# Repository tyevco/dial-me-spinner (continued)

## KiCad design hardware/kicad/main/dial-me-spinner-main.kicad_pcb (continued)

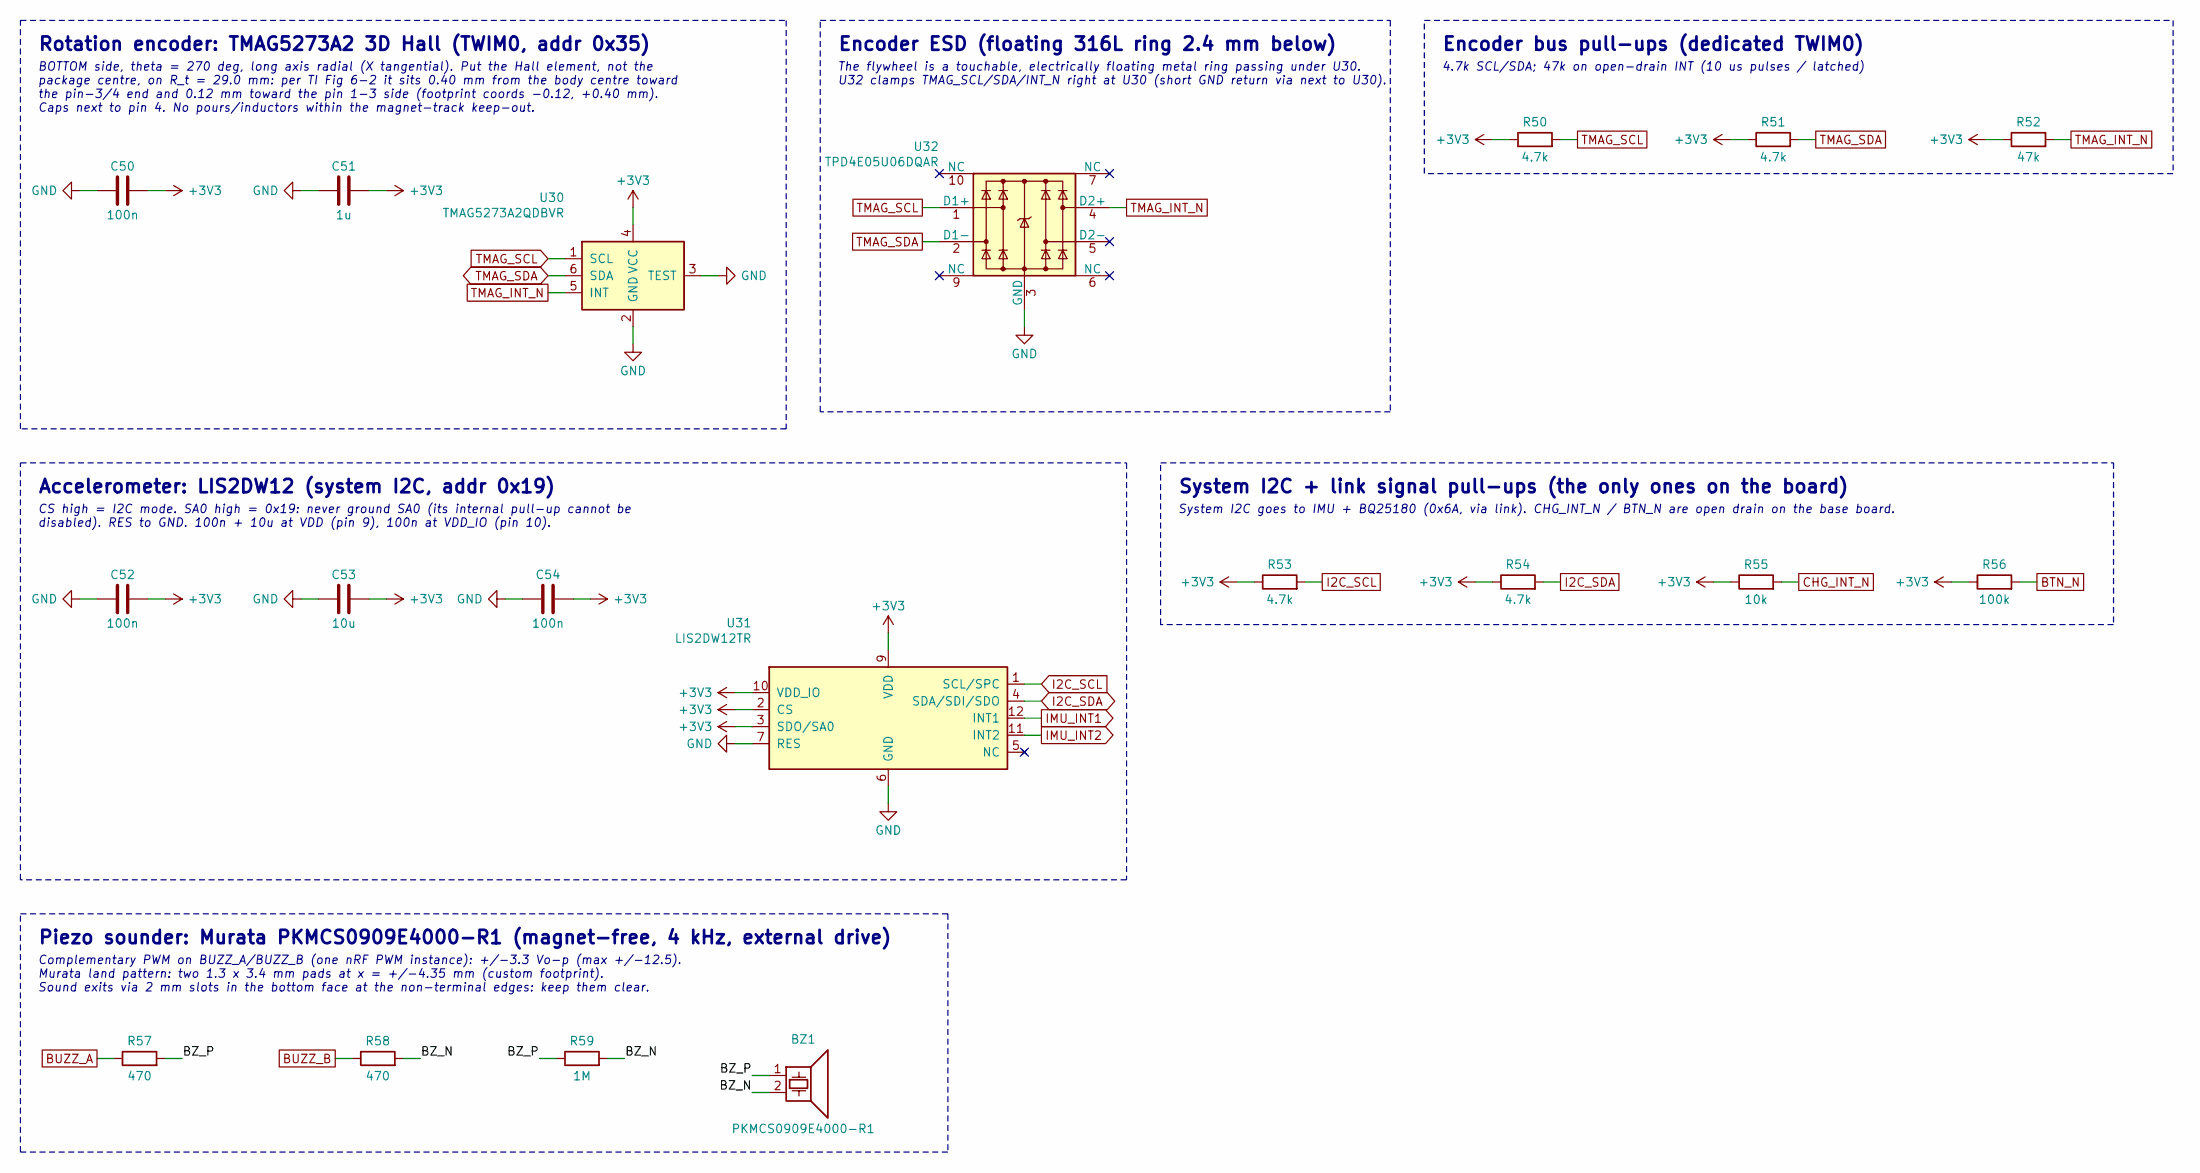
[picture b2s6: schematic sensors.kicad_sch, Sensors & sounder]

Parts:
BZ1: PKMCS0909E4000-R1; Buzzer_Murata_PKMCS0909E4000-R1; MPN PKMCS0909E4000-R1; LCSC C910763
C50, C52, C54: 100n; C_0402_1005Metric; MPN CL05B104KO5NNNC; LCSC C1525
C51: 1u; C_0402_1005Metric; MPN CL05A105KA5NQNC; LCSC C52923
C53: 10u; C_0603_1608Metric; MPN CL10A106KP8NNNC; LCSC C19702
R50, R51, R53, R54: 4.7k; R_0402_1005Metric; MPN 0402WGF4701TCE; LCSC C25900
R52: 47k; R_0402_1005Metric; MPN 0402WGF4702TCE; LCSC C25792
R55: 10k; R_0402_1005Metric; MPN 0402WGF1002TCE; LCSC C25744
R56: 100k; R_0402_1005Metric; MPN 0402WGF1003TCE; LCSC C25741
R57, R58: 470; R_0402_1005Metric; MPN 0402WGF4700TCE; LCSC C25117
R59: 1M; R_0402_1005Metric; MPN 0402WGF1004TCE; LCSC C26083
U30: TMAG5273A2QDBVR; SOT-23-6; MPN TMAG5273A2QDBVR; LCSC C3715882
U31: LIS2DW12TR; LGA-12_2x2mm_P0.5mm; MPN LIS2DW12TR; LCSC C189624
U32: TPD4E05U06DQAR; USON-10_2.5x1.0mm_P0.5mm; MPN TPD4E05U06DQAR; LCSC C138714

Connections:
+3V3: C50.2, C51.2, C52.2, C53.2, C54.2, R50.1, R51.1, R52.1, R53.1, R54.1, R55.1, R56.1, U30.4 (VCC), U31.2 (CS), U31.3 (SDO/SA0), U31.9 (VDD), U31.10 (VDD_IO); also elsewhere on the board
/Sensors & sounder/BZ_N: BZ1.2, R58.2, R59.2
/Sensors & sounder/BZ_P: BZ1.1, R57.2, R59.1
BTN_N: R56.2; also elsewhere on the board
BUZZ_A: R57.1; also elsewhere on the board
BUZZ_B: R58.1; also elsewhere on the board
CHG_INT_N: R55.2; also elsewhere on the board
GND: C50.1, C51.1, C52.1, C53.1, C54.1, U30.2 (GND), U30.3 (TEST), U31.6 (GND), U31.7 (RES), U31.8 (GND), U32.3 (GND), U32.8 (GND); also elsewhere on the board
I2C_SCL: R53.2, U31.1 (SCL/SPC); also elsewhere on the board
I2C_SDA: R54.2, U31.4 (SDA/SDI/SDO); also elsewhere on the board
IMU_INT1: U31.12 (INT1); also elsewhere on the board
IMU_INT2: U31.11 (INT2); also elsewhere on the board
TMAG_INT_N: R52.2, U30.5 (INT), U32.4 (D2+); also elsewhere on the board
TMAG_SCL: R50.2, U30.1 (SCL), U32.1 (D1+); also elsewhere on the board
TMAG_SDA: R51.2, U30.6 (SDA), U32.2 (D1-); also elsewhere on the board

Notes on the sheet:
Rotation encoder: TMAG5273A2 3D Hall (TWIM0, addr 0x35)
BOTTOM side, theta = 270 deg, long axis radial (X tangential). Put the Hall element, not the package centre, on R_t = 29.0 mm: per TI Fig 6-2 it sits 0.40 mm from the body centre toward the pin-3/4 end and 0.12 mm toward the pin 1-3 side (footprint coords -0.12, +0.40 mm). Caps next to pin 4. No po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
Encoder ESD (floating 316L ring 2.4 mm below)
The flywheel is a touchable, electrically floating metal ring passing under U30. U32 clamps TMAG_SCL/SDA/INT_N right at U30 (short GND return via next to U30).
Encoder bus pull-ups (dedicated TWIM0)
4.7k SCL/SDA; 47k on open-drain INT (10 us pulses / latched)
Accelerometer: LIS2DW12 (system I2C, addr 0x19)
CS high = I2C mode. SA0 high = 0x19: never ground SA0 (its internal pull-up cannot be disabled). RES to GND. 100n + 10u at VDD (pin 9), 100n at VDD_IO (pin 10).
System I2C + link signal pull-ups (the only ones on the board)
System I2C goes to IMU + BQ25180 (0x6A, via link). CHG_INT_N / BTN_N are open drain on the base board.
Piezo sounder: Murata PKMCS0909E4000-R1 (magnet-free, 4 kHz, external drive)
Complementary PWM on BUZZ_A/BUZZ_B (one nRF PWM instance): +/-3.3 Vo-p (max +/-12.5). Murata land pattern: two 1.3 x 3.4 mm pads at x = +/-4.35 mm (custom footprint). Sound exits via 2 mm slots in the bottom face at the non-terminal edges: keep them clear.

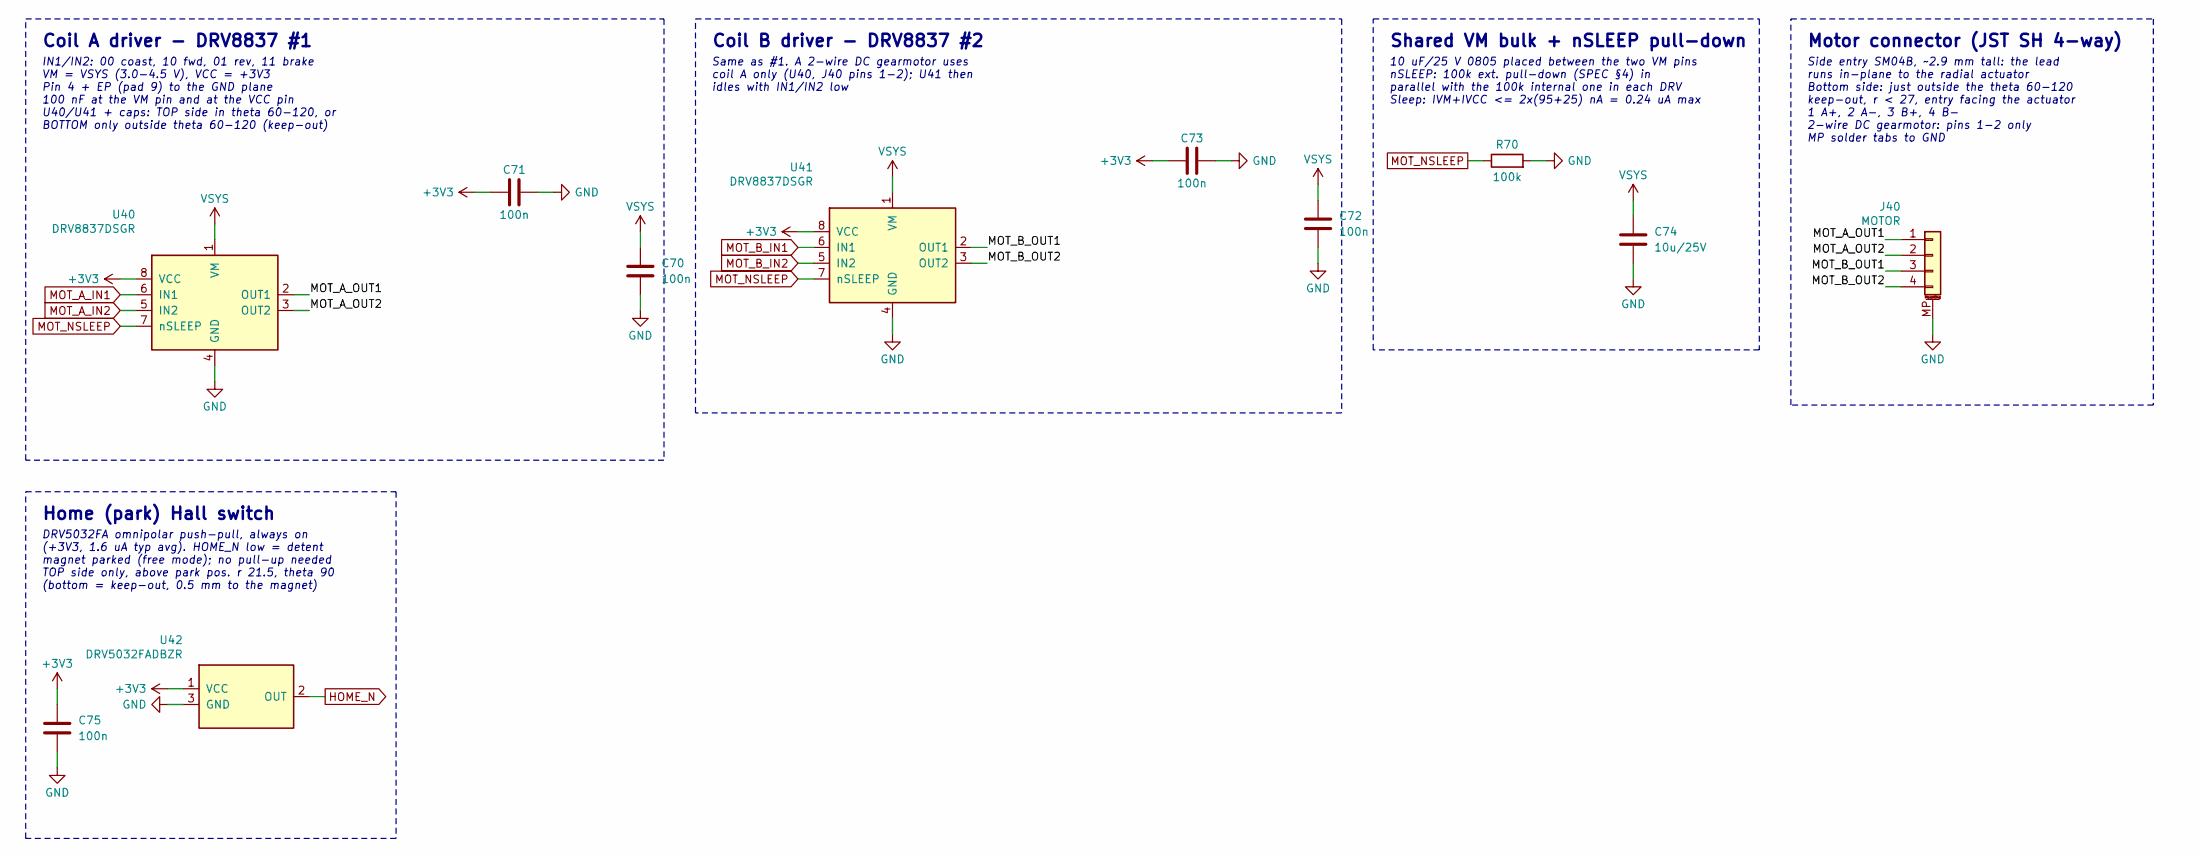
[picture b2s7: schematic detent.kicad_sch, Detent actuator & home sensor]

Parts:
C70, C71, C72, C73, C75: 100n; C_0402_1005Metric; MPN CL05B104KO5NNNC; LCSC C1525
C74: 10u/25V; C_0805_2012Metric; MPN CL21A106KAYNNNE; LCSC C15850
J40: MOTOR; JST_SH_SM04B-SRSS-TB_1x04-1MP_P1.00mm_Horizontal; MPN SM04B-SRSS-TB(LF)(SN); LCSC C160404
R70: 100k; R_0402_1005Metric; MPN 0402WGF1003TCE; LCSC C25741
U40, U41: DRV8837DSGR; Texas_DSG0008A_WSON-8-1EP_2x2mm_P0.5mm_EP0.9x1.6mm; MPN DRV8837DSGR; LCSC C39159
U42: DRV5032FADBZR; SOT-23; MPN DRV5032FADBZR; LCSC C140921

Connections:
+3V3: C71.1, C73.1, C75.1, U40.8 (VCC), U41.8 (VCC), U42.1 (VCC); also elsewhere on the board
/Detent actuator & home sensor/MOT_A_OUT1: J40.1, U40.2 (OUT1)
/Detent actuator & home sensor/MOT_A_OUT2: J40.2, U40.3 (OUT2)
/Detent actuator & home sensor/MOT_B_OUT1: J40.3, U41.2 (OUT1)
/Detent actuator & home sensor/MOT_B_OUT2: J40.4, U41.3 (OUT2)
GND: C70.2, C71.2, C72.2, C73.2, C74.2, C75.2, J40.MP (MountPin), R70.2, U40.4 (GND), U40.9 (GND), U41.4 (GND), U41.9 (GND), U42.3 (GND); also elsewhere on the board
HOME_N: U42.2 (OUT); also elsewhere on the board
MOT_A_IN1: U40.6 (IN1); also elsewhere on the board
MOT_A_IN2: U40.5 (IN2); also elsewhere on the board
MOT_B_IN1: U41.6 (IN1); also elsewhere on the board
MOT_B_IN2: U41.5 (IN2); also elsewhere on the board
MOT_NSLEEP: R70.1, U40.7 (nSLEEP), U41.7 (nSLEEP); also elsewhere on the board
VSYS: C70.1, C72.1, C74.1, U40.1 (VM), U41.1 (VM); also elsewhere on the board

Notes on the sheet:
Coil A driver - DRV8837 #1
IN1/IN2: 00 coast, 10 fwd, 01 rev, 11 brake VM = VSYS (3.0-4.5 V), VCC = +3V3 Pin 4 + EP (pad 9) to the GND plane 100 nF at the VM pin and at the VCC pin U40/U41 + caps: TOP side in theta 60-120, or BOTTOM only outside theta 60-120 (keep-out)
Coil B driver - DRV8837 #2
Same as #1. A 2-wire DC gearmotor uses coil A only (U40, J40 pins 1-2); U41 then idles with IN1/IN2 low
Shared VM bulk + nSLEEP pull-down
10 uF/25 V 0805 placed between the two VM pins nSLEEP: 100k ext. pull-down (SPEC §4) in parallel with the 100k internal one in each DRV Sleep: IVM+IVCC <= 2x(95+25) nA = 0.24 uA max
Motor connector (JST SH 4-way)
Side entry SM04B, ~2.9 mm tall: the lead runs in-plane to the radial actuator Bottom side: just outside the theta 60-120 keep-out, r < 27, entry facing the actuator 1 A+, 2 A-, 3 B+, 4 B- 2-wire DC gearmotor: pins 1-2 only MP solder tabs to GND
Home (park) Hall switch
DRV5032FA omnipolar push-pull, always on (+3V3, 1.6 uA typ avg). HOME_N low = detent magnet parked (free mode); no pull-up needed TOP side only, above park pos. r 21.5, theta 90 (bottom = keep-out, 0.5 mm to the magnet)

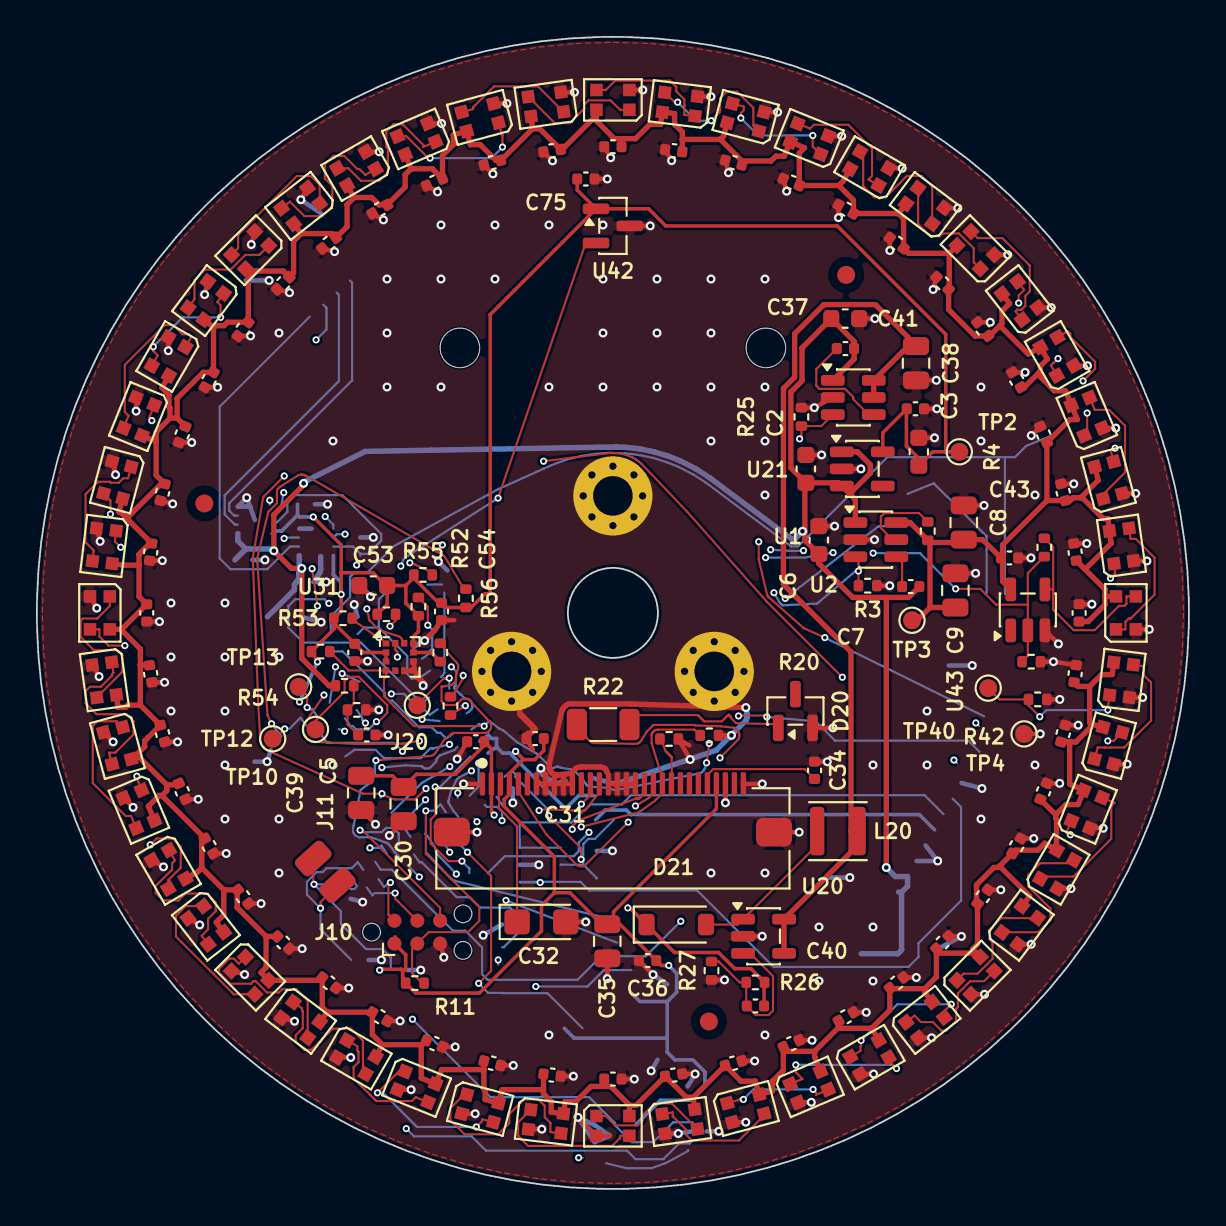
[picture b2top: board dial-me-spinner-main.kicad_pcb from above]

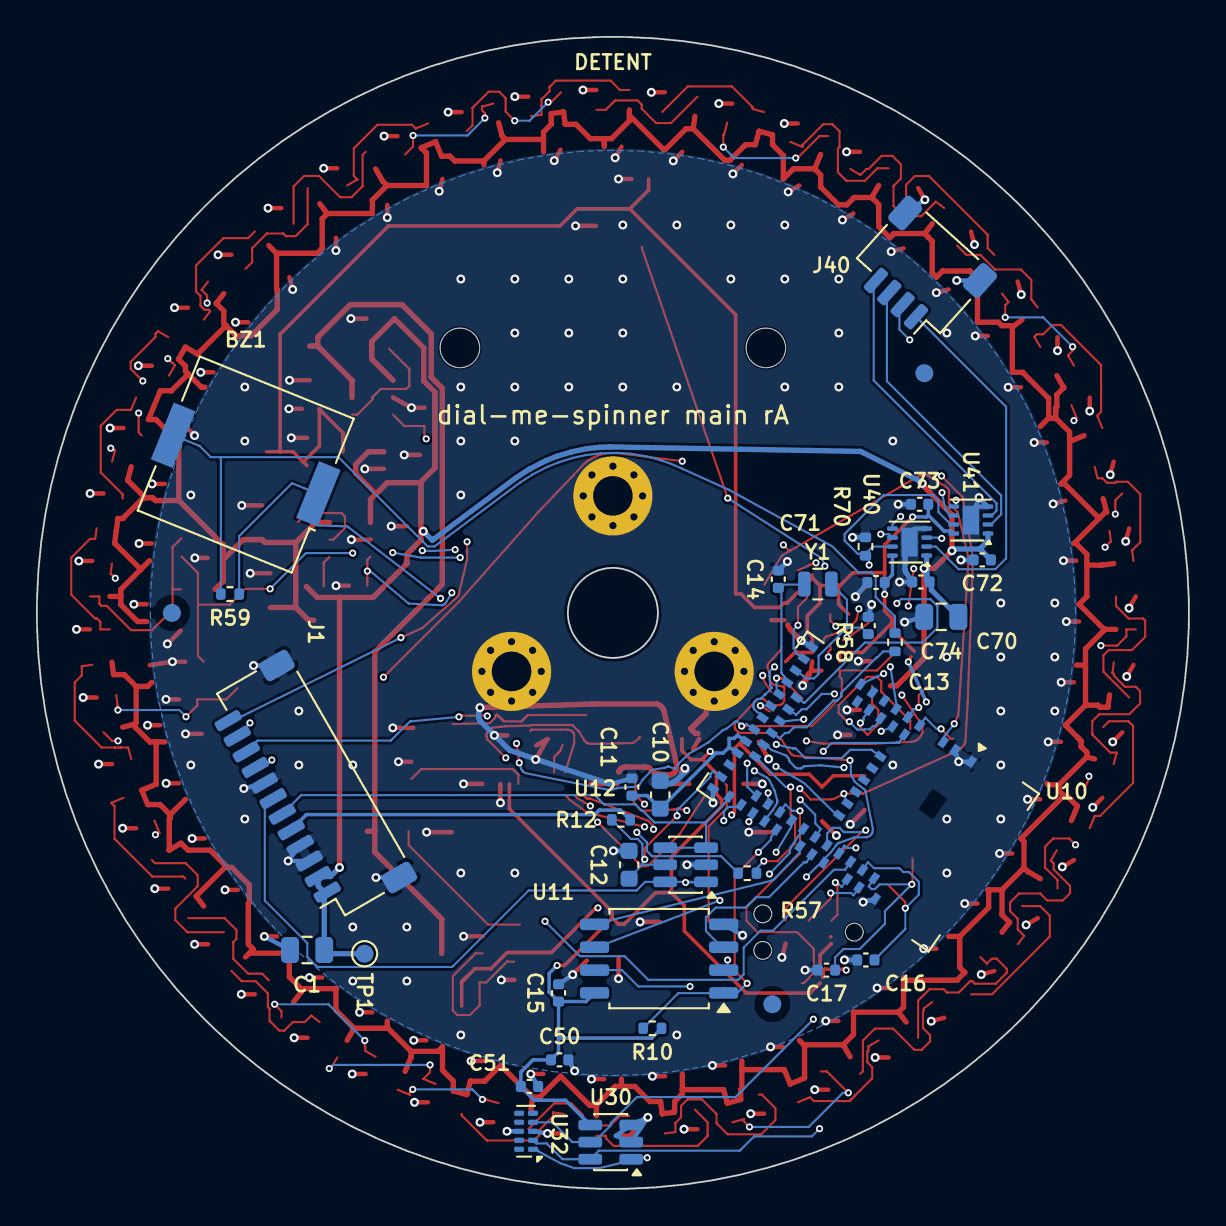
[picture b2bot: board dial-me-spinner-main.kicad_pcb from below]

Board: 4 copper layers, 64.0 x 64.0 mm, 209 parts (37 on the bottom side), 120 nets.

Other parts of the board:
FID1, FID2, FID3, FID4, FID5, FID6: Fiducial_1mm_Mask2mm
H4, H5: MountingHole_2.2mm_M2

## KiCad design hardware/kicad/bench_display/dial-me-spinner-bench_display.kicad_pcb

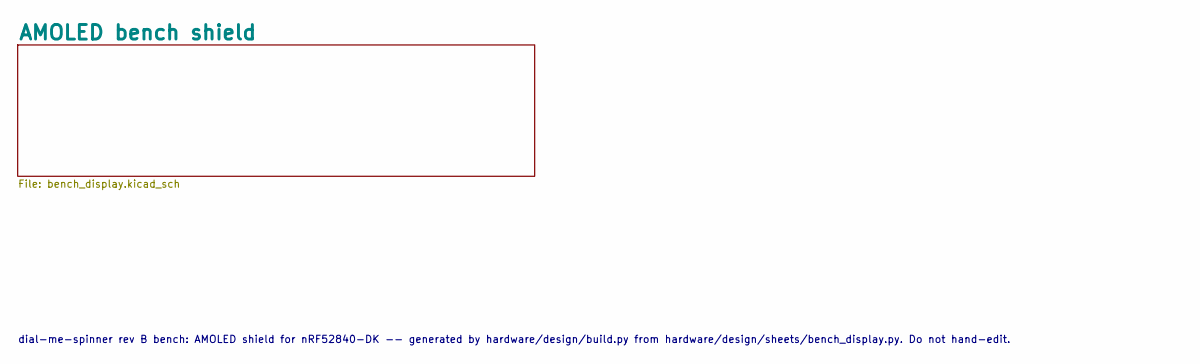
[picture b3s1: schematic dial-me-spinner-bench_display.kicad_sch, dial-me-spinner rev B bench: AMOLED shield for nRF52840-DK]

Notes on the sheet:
dial-me-spinner rev B bench: AMOLED shield for nRF52840-DK -- generated by hardware/design/build.py from hardware/design/sheets/bench_display.py. Do not hand-edit.

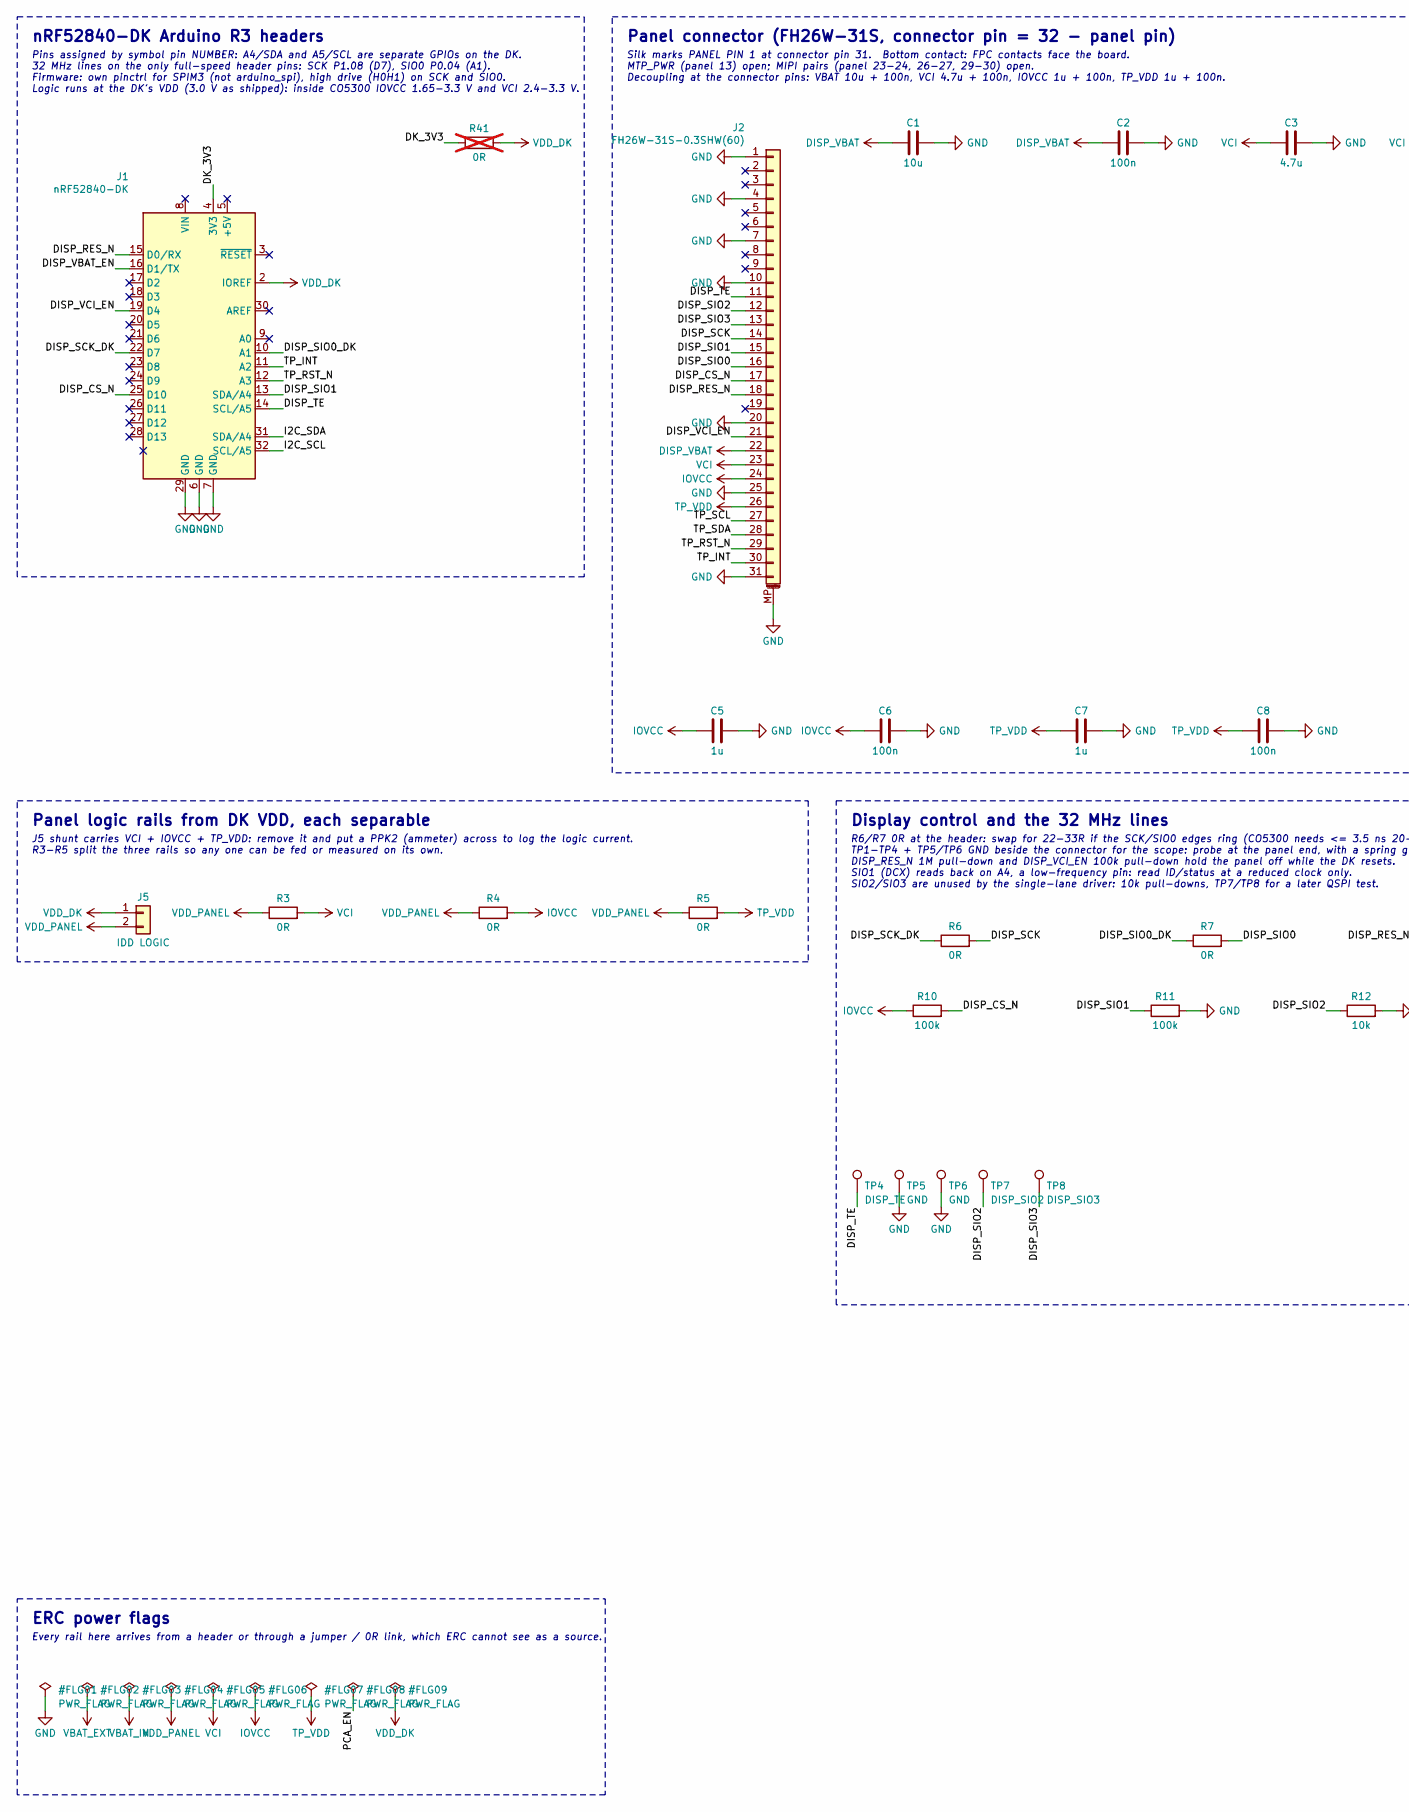
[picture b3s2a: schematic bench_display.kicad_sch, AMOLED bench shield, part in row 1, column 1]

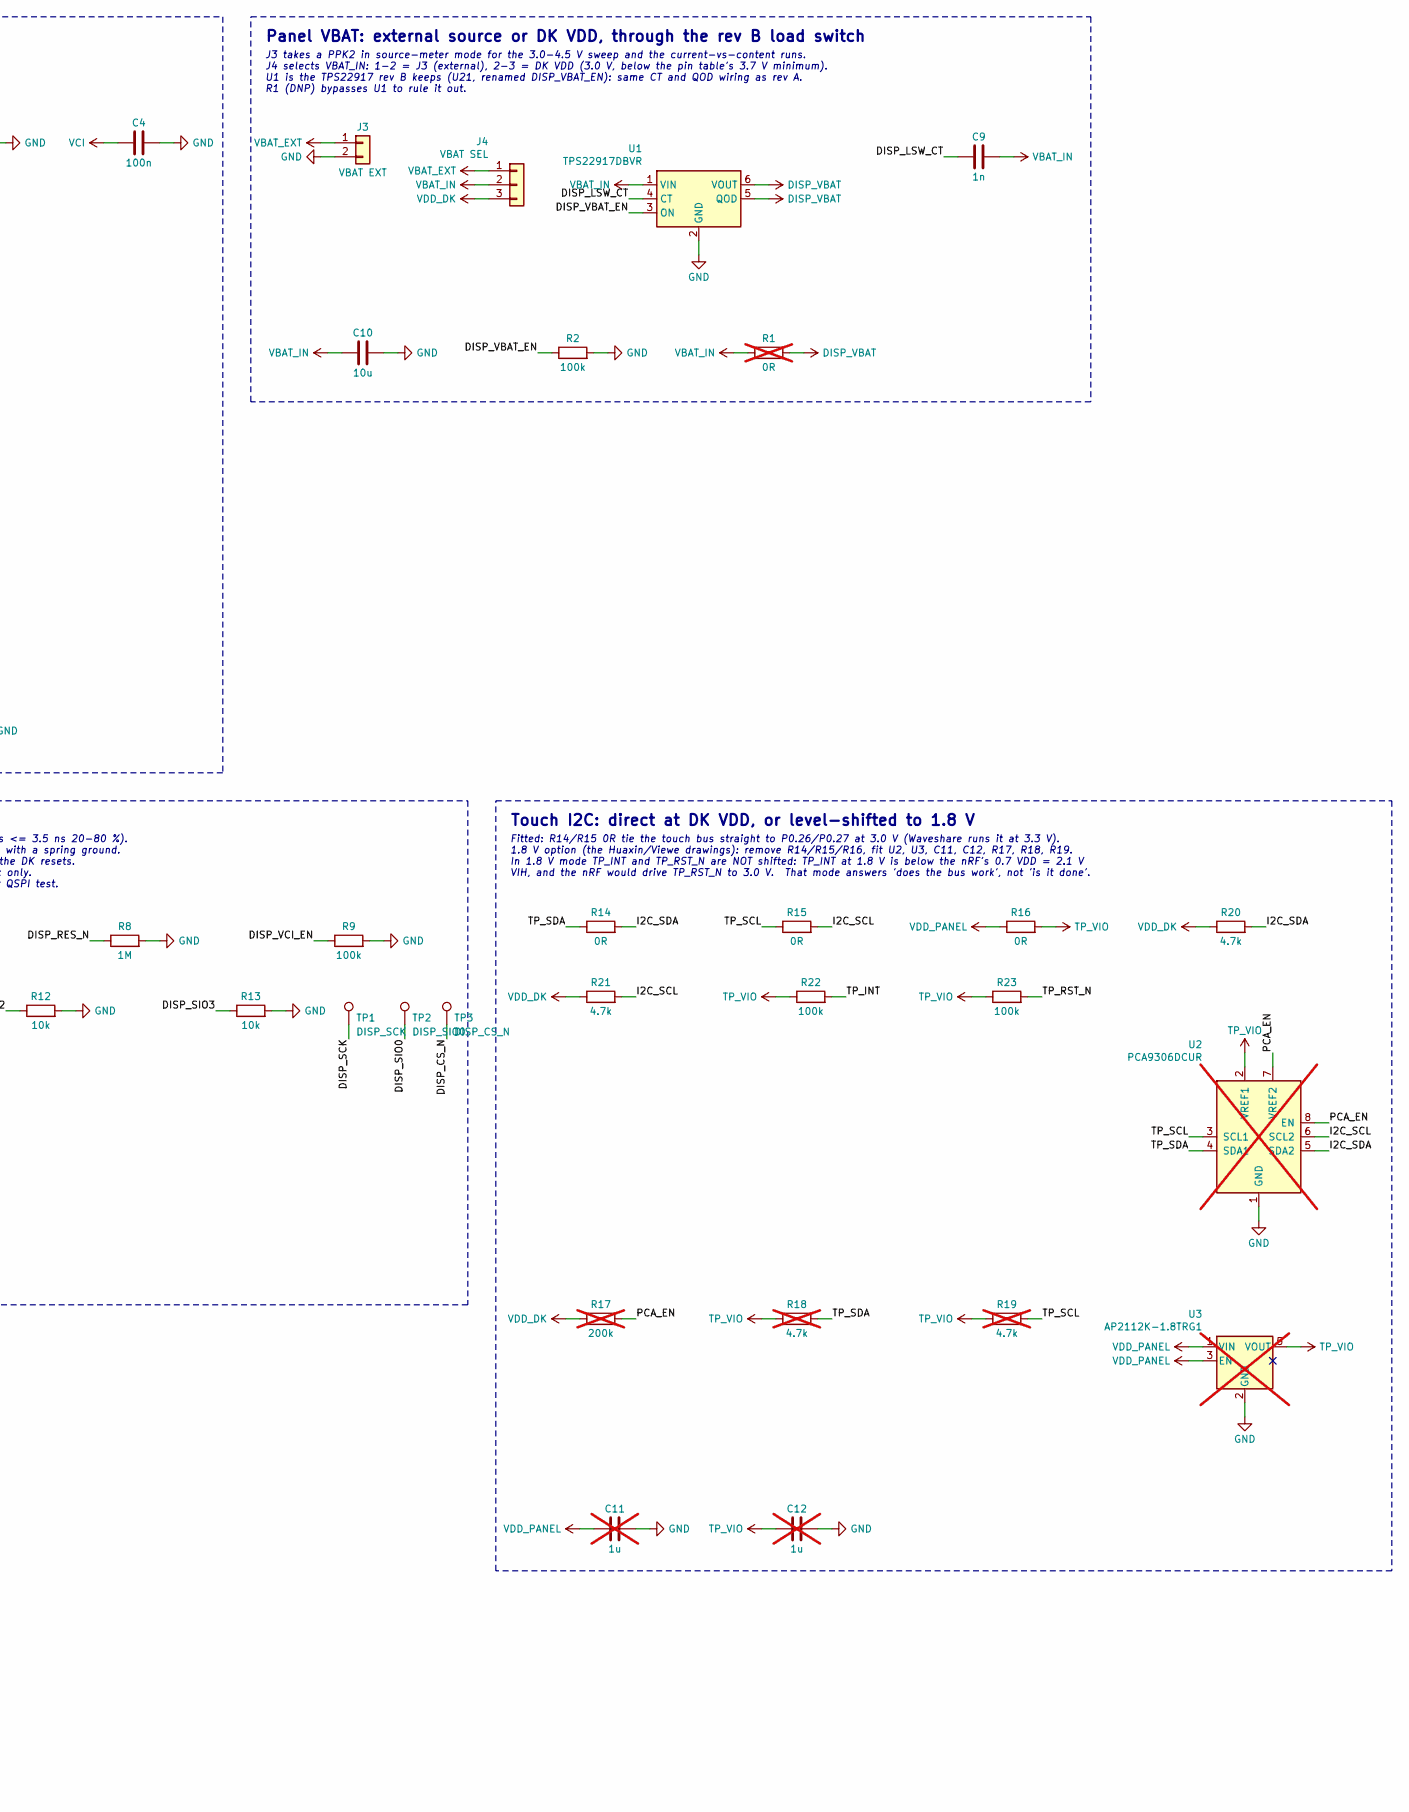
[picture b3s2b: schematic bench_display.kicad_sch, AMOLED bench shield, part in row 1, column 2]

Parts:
C1, C10: 10u; C_0603_1608Metric; MPN CL10A106MA8NRNC; LCSC C96446
C2, C4, C6, C8: 100n; C_0402_1005Metric; MPN CL05B104KO5NNNC; LCSC C1525
C3: 4.7u; C_0805_2012Metric; MPN CL21A475KAQNNNE; LCSC C1779
C5, C7: 1u; C_0402_1005Metric; MPN CL05A105KA5NQNC; LCSC C52923
C9: 1n; C_0402_1005Metric; MPN 0402B102K500NT; LCSC C1523
C11, C12: 1u; C_0402_1005Metric; MPN CL05A105KA5NQNC; LCSC C52923; not fitted
J1: nRF52840-DK; Arduino_UNO_R3
J2: FH26W-31S-0.3SHW(60); Hirose_FH26-31S-0.3SHW_2Rows-31Pins-1MP_P0.60mm_Horizontal; MPN FH26W-31S-0.3SHW(60); LCSC C2973806
J3: VBAT EXT; PinHeader_1x02_P2.54mm_Vertical
J4: VBAT SEL; PinHeader_1x03_P2.54mm_Vertical
J5: IDD LOGIC; PinHeader_1x02_P2.54mm_Vertical
R1, R41: 0R; R_0402_1005Metric; MPN 0402WGF0000TCE; LCSC C17168; not fitted
R2, R9, R10, R11, R22, R23: 100k; R_0402_1005Metric; MPN 0402WGF1003TCE; LCSC C25741
R3, R4, R5, R6, R7, R14, R15, R16: 0R; R_0402_1005Metric; MPN 0402WGF0000TCE; LCSC C17168
R8: 1M; R_0402_1005Metric; MPN 0402WGF1004TCE; LCSC C26083
R12, R13: 10k; R_0402_1005Metric; MPN 0402WGF1002TCE; LCSC C25744
R17: 200k; R_0402_1005Metric; MPN 0402WGF2003TCE; LCSC C25764; not fitted
R18, R19: 4.7k; R_0402_1005Metric; MPN 0402WGF4701TCE; LCSC C25900; not fitted
R20, R21: 4.7k; R_0402_1005Metric; MPN 0402WGF4701TCE; LCSC C25900
TP1: DISP_SCK; TestPoint_Pad_D1.0mm
TP2: DISP_SIO0; TestPoint_Pad_D1.0mm
TP3: DISP_CS_N; TestPoint_Pad_D1.0mm
TP4: DISP_TE; TestPoint_Pad_D1.0mm
TP5, TP6: GND; TestPoint_Pad_D1.0mm
TP7: DISP_SIO2; TestPoint_Pad_D1.0mm
TP8: DISP_SIO3; TestPoint_Pad_D1.0mm
U1: TPS22917DBVR; SOT-23-6; MPN TPS22917DBVR; LCSC C2681320
U2: PCA9306DCUR; VSSOP-8_2.3x2mm_P0.5mm; MPN PCA9306DCUR; LCSC C33196; not fitted
U3: AP2112K-1.8TRG1; SOT-23-5; MPN AP2112K-1.8TRG1; LCSC C176944; not fitted

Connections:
/AMOLED bench shield/DISP_CS_N: J1.25 (D10), J2.17, R10.2, TP3.1
/AMOLED bench shield/DISP_LSW_CT: C9.1, U1.4 (CT)
/AMOLED bench shield/DISP_RES_N: J1.15 (D0/RX), J2.18, R8.1
/AMOLED bench shield/DISP_SCK: J2.14, R6.2, TP1.1
/AMOLED bench shield/DISP_SCK_DK: J1.22 (D7), R6.1
/AMOLED bench shield/DISP_SIO0: J2.16, R7.2, TP2.1
/AMOLED bench shield/DISP_SIO0_DK: J1.10 (A1), R7.1
/AMOLED bench shield/DISP_SIO1: J1.13 (SDA/A4), J2.15, R11.1
/AMOLED bench shield/DISP_SIO2: J2.12, R12.1, TP7.1
/AMOLED bench shield/DISP_SIO3: J2.13, R13.1, TP8.1
/AMOLED bench shield/DISP_TE: J1.14 (SCL/A5), J2.11, TP4.1
/AMOLED bench shield/DISP_VBAT_EN: J1.16 (D1/TX), R2.1, U1.3 (ON)
/AMOLED bench shield/DISP_VCI_EN: J1.19 (D4), J2.21, R9.1
/AMOLED bench shield/DK_3V3: J1.4 (3V3), R41.1
/AMOLED bench shield/I2C_SCL: J1.32 (SCL/A5), R15.2, R21.2, U2.6 (SCL2)
/AMOLED bench shield/I2C_SDA: J1.31 (SDA/A4), R14.2, R20.2, U2.5 (SDA2)
/AMOLED bench shield/PCA_EN: R17.2, U2.7 (VREF2), U2.8 (EN)
/AMOLED bench shield/TP_INT: J1.11 (A2), J2.30, R22.2
/AMOLED bench shield/TP_RST_N: J1.12 (A3), J2.29, R23.2
/AMOLED bench shield/TP_SCL: J2.27, R15.1, R19.2, U2.3 (SCL1)
/AMOLED bench shield/TP_SDA: J2.28, R14.1, R18.2, U2.4 (SDA1)
DISP_VBAT: C1.1, C2.1, J2.22, R1.2, U1.5 (QOD), U1.6 (VOUT)
GND: C1.2, C2.2, C3.2, C4.2, C5.2, C6.2, C7.2, C8.2, C10.2, C11.2, C12.2, J1.6 (GND), J1.7 (GND), J1.29 (GND), J2.1, J2.4, J2.7, J2.10, J2.20, J2.25, J2.31, J2.MP (MountPin), J3.2, R2.2, R8.2, R9.2, R11.2, R12.2, R13.2, TP5.1, TP6.1, U1.2 (GND), U2.1 (GND), U3.2 (GND)
IOVCC: C5.1, C6.1, J2.24, R4.2, R10.1
TP_VDD: C7.1, C8.1, J2.26, R5.2
TP_VIO: C12.1, R16.2, R18.1, R19.1, R22.1, R23.1, U2.2 (VREF1), U3.5 (VOUT)
VBAT_EXT: J3.1, J4.1
VBAT_IN: C9.2, C10.1, J4.2, R1.1, U1.1 (VIN)
VCI: C3.1, C4.1, J2.23, R3.2
VDD_DK: J1.2 (IOREF), J4.3, J5.1, R17.1, R20.1, R21.1, R41.2
VDD_PANEL: C11.1, J5.2, R3.1, R4.1, R5.1, R16.1, U3.1 (VIN), U3.3 (EN)

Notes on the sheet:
nRF52840-DK Arduino R3 headers
Pins assigned by symbol pin NUMBER: A4/SDA and A5/SCL are separate GPIOs on the DK. 32 MHz lines on the only full-speed header pins: SCK P1.08 (D7), SIO0 P0.04 (A1). Firmware: own pinctrl for SPIM3 (not arduino_spi), high drive (H0H1) on SCK and SIO0. Logic runs at the DK's VDD (3.0 V as shipped): 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
Panel connector (FH26W-31S, connector pin = 32 - panel pin)
Silk marks PANEL PIN 1 at connector pin 31. Bottom contact: FPC contacts face the board. MTP_PWR (panel 13) open; MIPI pairs (panel 23-24, 26-27, 29-30) open. Decoupling at the connector pins: VBAT 10u + 100n, VCI 4.7u + 100n, IOVCC 1u + 100n, TP_VDD 1u + 100n.
Panel VBAT: external source or DK VDD, through the rev B load switch
J3 takes a PPK2 in source-meter mode for the 3.0-4.5 V sweep and the current-vs-content runs. J4 selects VBAT_IN: 1-2 = J3 (external), 2-3 = DK VDD (3.0 V, below the pin table's 3.7 V minimum). U1 is the TPS22917 rev B keeps (U21, renamed DISP_VBAT_EN): same CT and QOD wiring as rev A. R1 (DNP) byp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
Panel logic rails from DK VDD, each separable
J5 shunt carries VCI + IOVCC + TP_VDD: remove it and put a PPK2 (ammeter) across to log the logic current. R3-R5 split the three rails so any one can be fed or measured on its own.
Display control and the 32 MHz lines
R6/R7 0R at the header: swap for 22-33R if the SCK/SIO0 edges ring (CO5300 needs <= 3.5 ns 20-80 %). TP1-TP4 + TP5/TP6 GND beside the connector for the scope: probe at the panel end, with a spring ground. DISP_RES_N 1M pull-down and DISP_VCI_EN 100k pull-down hold the panel off while the DK resets.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
Touch I2C: direct at DK VDD, or level-shifted to 1.8 V
Fitted: R14/R15 0R tie the touch bus straight to P0.26/P0.27 at 3.0 V (Waveshare runs it at 3.3 V). 1.8 V option (the Huaxin/Viewe drawings): remove R14/R15/R16, fit U2, U3, C11, C12, R17, R18, R19. In 1.8 V mode TP_INT and TP_RST_N are NOT shifted: TP_INT at 1.8 V is below the nRF's 0.7 VDD = 2.1 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
ERC power flags
Every rail here arrives from a header or through a jumper / 0R link, which ERC cannot see as a source.

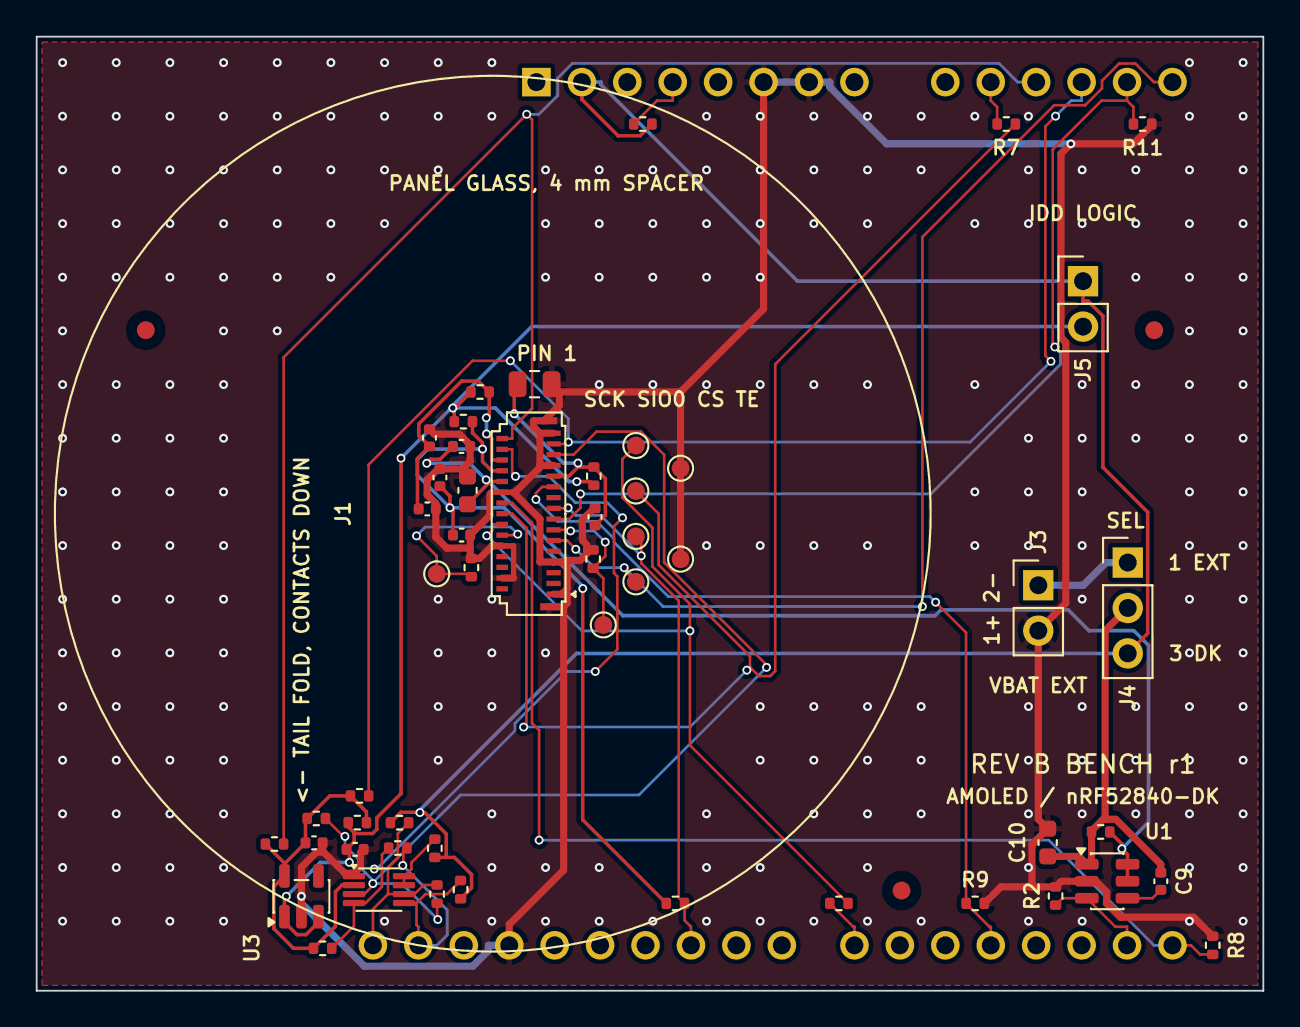
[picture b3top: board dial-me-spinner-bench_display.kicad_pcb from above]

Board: 2 copper layers, 68.6 x 53.3 mm, 55 parts (0 on the bottom side), 31 nets.

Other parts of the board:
FID1, FID2, FID3: Fiducial_1mm_Mask2mm

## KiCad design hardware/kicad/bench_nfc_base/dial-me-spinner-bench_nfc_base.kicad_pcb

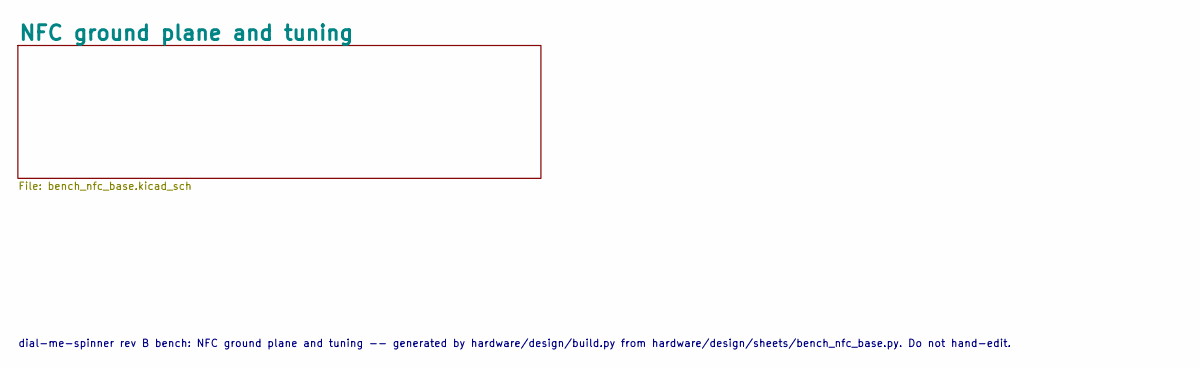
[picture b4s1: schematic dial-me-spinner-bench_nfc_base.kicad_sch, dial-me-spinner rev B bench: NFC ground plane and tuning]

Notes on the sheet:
dial-me-spinner rev B bench: NFC ground plane and tuning -- generated by hardware/design/build.py from hardware/design/sheets/bench_nfc_base.py. Do not hand-edit.
